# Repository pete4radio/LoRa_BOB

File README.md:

# LoRa_BOB
RFM9x feather with PCB 900 MHz antenna

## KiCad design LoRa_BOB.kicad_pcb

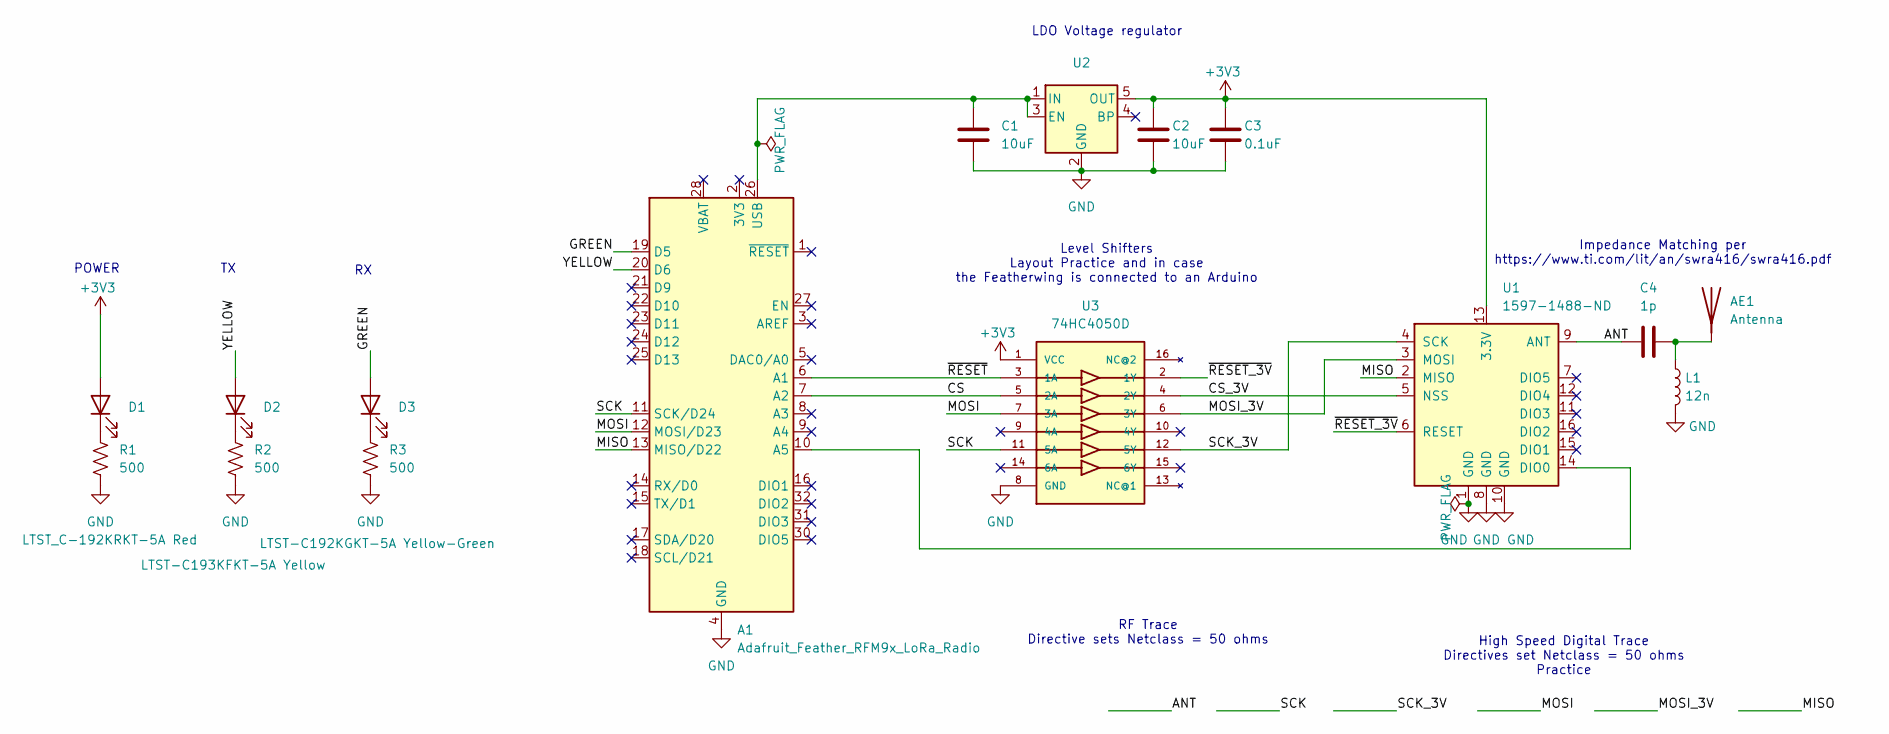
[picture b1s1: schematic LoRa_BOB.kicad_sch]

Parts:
A1: Adafruit_Feather_RFM9x_LoRa_Radio; Adafruit_Feather_M0_RFM
AE1: Antenna; Texas_SWRA416_868MHz_915MHz
C1, C2: 10uF; C_1206_3216Metric_Pad1.33x1.80mm_HandSolder
C3: 0.1uF; C_0805_2012Metric_Pad1.18x1.45mm_HandSolder
C4: 1p; C_0603_1608Metric_Pad1.08x0.95mm_HandSolder
D1: LTST_C-192KRKT-5A Red; LED_0603_1608Metric_Pad1.05x0.95mm_HandSolder
D2: LTST-C193KFKT-5A Yellow; LED_0603_1608Metric_Pad1.05x0.95mm_HandSolder
D3: LTST-C192KGKT-5A Yellow-Green; LED_0603_1608Metric_Pad1.05x0.95mm_HandSolder
L1: 12n; L_0603_1608Metric_Pad1.05x0.95mm_HandSolder
R1, R2, R3: 500; R_0603_1608Metric_Pad0.98x0.95mm_HandSolder
U1: 1597-1488-ND; HOPERF_RFM9XW_SMD
U2: XC6210B332MR-G; SOT-23-5
U3: 74HC4050D; SOIC-16_3.9x9.9mm_P1.27mm; DigiKey_Part_Number 74HC4050DCT-ND

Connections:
+3V3: C2.1, C3.1, D1.2 (A), U1.13 (3.3V), U2.5 (OUT), U3.1 (VCC)
/ANT: C4.1, U1.9 (ANT)
/CS: A1.7 (A2), U3.5 (2A)
/CS_3V: U1.5 (NSS), U3.4 (2Y)
/GREEN: A1.19 (D5), D3.2 (A)
/MISO: A1.13 (MISO/D22), U1.2 (MISO)
/MOSI: A1.12 (MOSI/D23), U3.7 (3A)
/MOSI_3V: U1.3 (MOSI), U3.6 (3Y)
/SCK: A1.11 (SCK/D24), U3.11 (5A)
/SCK_3V: U1.4 (SCK), U3.12 (5Y)
/YELLOW: A1.20 (D6), D2.2 (A)
/~RESET_3V: U1.6 (RESET), U3.2 (1Y)
/~RESET: A1.6 (A1), U3.3 (1A)
GND: A1.4 (GND), C1.2, C2.2, C3.2, L1.2, R1.2, R2.2, R3.2, U1.1 (GND), U1.8 (GND), U1.10 (GND), U2.2 (GND), U3.8 (GND)
unnamed: A1.10 (A5), U1.14 (DIO0)
unnamed: A1.26 (USB), C1.1, U2.1 (IN), U2.3 (EN)
unnamed: AE1.1 (A), C4.2, L1.1
unnamed: D1.1 (K), R1.1
unnamed: D2.1 (K), R2.1
unnamed: D3.1 (K), R3.1

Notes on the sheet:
POWER
Level Shifters Layout Practice and in case the Featherwing is connected to an Arduino
High Speed Digital Trace Directives set Netclass = 50 ohms Practice
Impedance Matching per https://www.ti.com/lit/an/swra416/swra416.pdf
RF Trace Directive sets Netclass = 50 ohms
LDO Voltage regulator

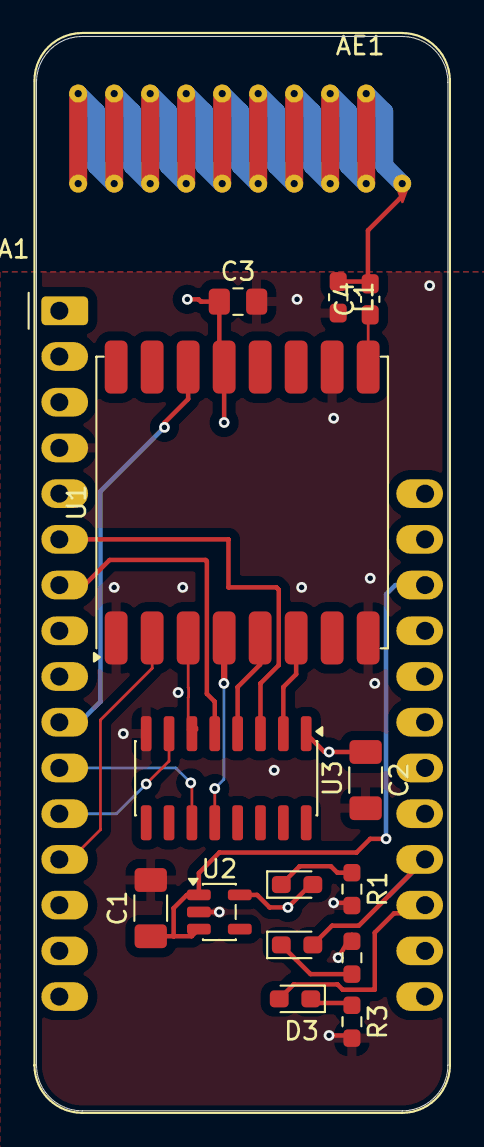
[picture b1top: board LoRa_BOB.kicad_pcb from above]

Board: 4 copper layers, 22.9 x 59.7 mm, 16 parts (0 on the bottom side), 20 nets.

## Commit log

2026-02-08 initial outline
2026-02-13 Added regulator and placed level shifters
2026-02-14 Minor advances
2026-02-14 Routed but could be better
2026-02-14 New Template
2026-02-14 basic, with trick Feather and RFM
2026-02-14 edited existing footprints and symbol
2026-02-15 pours
2026-02-15 netclass routing
2026-02-15 netclass directive cleanup
2026-02-15 better routing
2026-02-16 Better netclasses and 50 ohm trace widths
2026-02-16 LEDs
2026-02-16 better LEDs
2026-02-17 Power Flags
2026-02-17 LEDs were placed on PCB
2026-02-17 R's are 0603
2026-02-17 Added Antenna Matching L and C
